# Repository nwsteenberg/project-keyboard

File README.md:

# DIY Keyboards

A collection of resources from my journey into building my own mechanical keyboard.

## Keyboard Projects:
- [NordWingV1](https://github.com/nwsteenberg/project-keyboard/tree/main/NordWingV1)

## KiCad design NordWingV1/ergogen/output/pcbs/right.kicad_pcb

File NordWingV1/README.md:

# NordWingV1

My first fully DIY mechanical keyboard.

## Goals
- [x] Split. To have flexability in positions.
- [x] Nordic Layout. Will be used for software development, but since i am Danish the æøå are essential for daily use, and should not be put into a seperate layer.
- [x] Silent. Will be used at an open office so no clicky keys.
- [X] Simple. Thumb keys might be nice, but i don't want an F16 cockpit on my thumbs. 1-2 keys should be enough.
- [X] Ortholinear & Column staggered.

## Progress:

### Layout
First thing is layout. How many columns and rows do i neeed? I took a normal ISO nordic layout in [keyboard-layout-editor.com](keyboard-layout-editor.com), then started splitting, removing, moving and adding keys till i had something i was happy with.

I ended up with something like this:

I think it is rather simple. No complicated layers. I moved the arrow keys and some of the lessor used function keys like HOME, PGUP, PGDN etc. to a second layer since i might use them, but not every day. It is ortholinear and column staggered. Nordic layout and split.

### Ergogen
Next thing is Ergogen. Ergogen defines everything from the layout, to the PCBs to the case of the keyboard.

The complete Ergogen config can be found here: [config.yaml](ergogen/config.yaml)
This can generate the PCBs located at: [PCB](PCB)
And the case files (i converted them to .stl and centered them, but nothing more): [Blender](Blender)

### Parts
The following parts were used:
| Part  | Link |
| ------------- | ------------- |
| RP2040 USB-C  | https://www.aliexpress.com/item/1005003753933847.html  |
| Outemu Honey Peach V3 40g Linear Switches | https://www.aliexpress.com/item/1005008882662753.html  |
| Diodes  | https://www.aliexpress.com/item/4000685043735.html |
| Keycaps  | https://www.aliexpress.com/item/1005001928651798.html  |
| TRRS Connector  | [https://www.aliexpress.com/item/1005003753933847.html  |

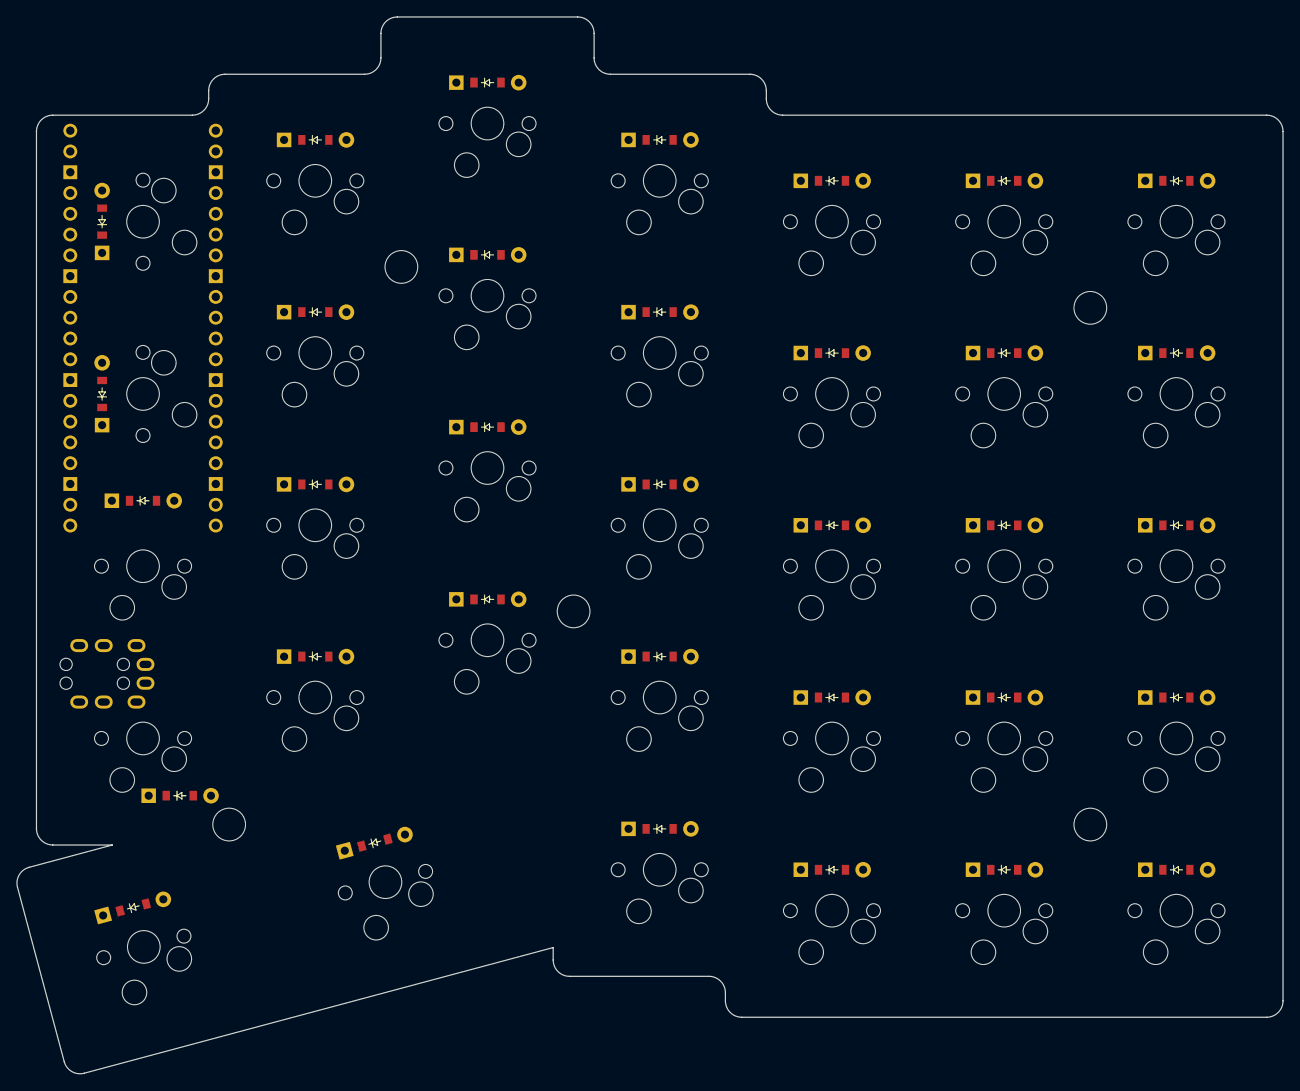
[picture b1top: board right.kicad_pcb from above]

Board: 2 copper layers, 154.7 x 129.2 mm, 70 parts (0 on the bottom side), 50 nets, no tracks yet.

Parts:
D1, D2, D3, D4, D5, D6, D7, D8, D9, D10, D11, D12, D13, D14, D15, D16, D17, D18, D19, D20, D21, D22, D23, D24, D25, D26, D27, D28, D29, D30, D31, D32, D33, D34: ComboDiode
S1, S2, S3, S4, S5, S6, S7, S8, S9, S10, S11, S12, S13, S14, S15, S16, S17, S18, S19, S20, S21, S22, S23, S24, S25, S26, S27, S28, S29, S30, S31, S32, S33, S34: MX
TRRS1: TRRS-PJ-320A-dual
_1: RPi_Pico_SMD_TH

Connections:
3V3: TRRS1.4, _1.36
GND: TRRS1.3, _1.3, _1.8, _1.13, _1.18, _1.23, _1.28, _1.38
GP0: TRRS1.1, _1.1
GP1: TRRS1.2, _1.2
GP6: S1.1, S2.1, S31.1, S33.1, S34.1, _1.9
GP7: S3.1, S4.1, S5.1, S6.1, S32.1, _1.10
GP8: S7.1, S8.1, S9.1, S10.1, _1.11
GP9: S11.1, S12.1, S13.1, S14.1, S15.1, _1.12
GP10: S16.1, S17.1, S18.1, S19.1, S20.1, _1.14
GP11: S21.1, S22.1, S23.1, S24.1, S25.1, _1.15
GP12: S26.1, S27.1, S28.1, S29.1, S30.1, _1.16
GP16: D9.1, D14.1, D19.1, D24.1, D29.1, D30.1, _1.21
GP17: D1.1, D5.1, D10.1, D15.1, D20.1, D25.1, D34.1, _1.22
GP18: D2.1, D6.1, D11.1, D16.1, D21.1, D26.1, D33.1, _1.24
GP19: D3.1, D7.1, D12.1, D17.1, D22.1, D27.1, D31.1, _1.25
GP20: D4.1, D8.1, D13.1, D18.1, D23.1, D28.1, D32.1, _1.26
back_space_default: D29.2, S31.2
enter_default: D30.2, S32.2
index_bottom: D1.2, S3.2
index_home: D2.2, S4.2
index_num: D4.2, S6.2
index_top: D3.2, S5.2
inner_bottom: D34.2, S1.2
inner_home: D33.2, S2.2
inner_num: D32.2, S34.2
inner_top: D31.2, S33.2
middle_bottom: D5.2, S7.2
middle_home: D6.2, S8.2
middle_num: D8.2, S10.2
middle_top: D7.2, S9.2
pinky_bottom: D15.2, S17.2
pinky_home: D16.2, S18.2
pinky_num: D18.2, S20.2
pinky_thumb: D14.2, S16.2
pinky_top: D17.2, S19.2
right2_bottom: D25.2, S27.2
right2_home: D26.2, S28.2
right2_num: D28.2, S30.2
right2_thumb: D24.2, S26.2
right2_top: D27.2, S29.2
right_bottom: D20.2, S22.2
right_home: D21.2, S23.2
right_num: D23.2, S25.2
right_thumb: D19.2, S21.2
right_top: D22.2, S24.2
ring_bottom: D10.2, S12.2
ring_home: D11.2, S13.2
ring_num: D13.2, S15.2
ring_thumb: D9.2, S11.2
ring_top: D12.2, S14.2

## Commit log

2025-08-13 initial commit. Added everything
2025-08-16 Rename NordWingV1/kle.png to NordWingV1/res/kle.png
